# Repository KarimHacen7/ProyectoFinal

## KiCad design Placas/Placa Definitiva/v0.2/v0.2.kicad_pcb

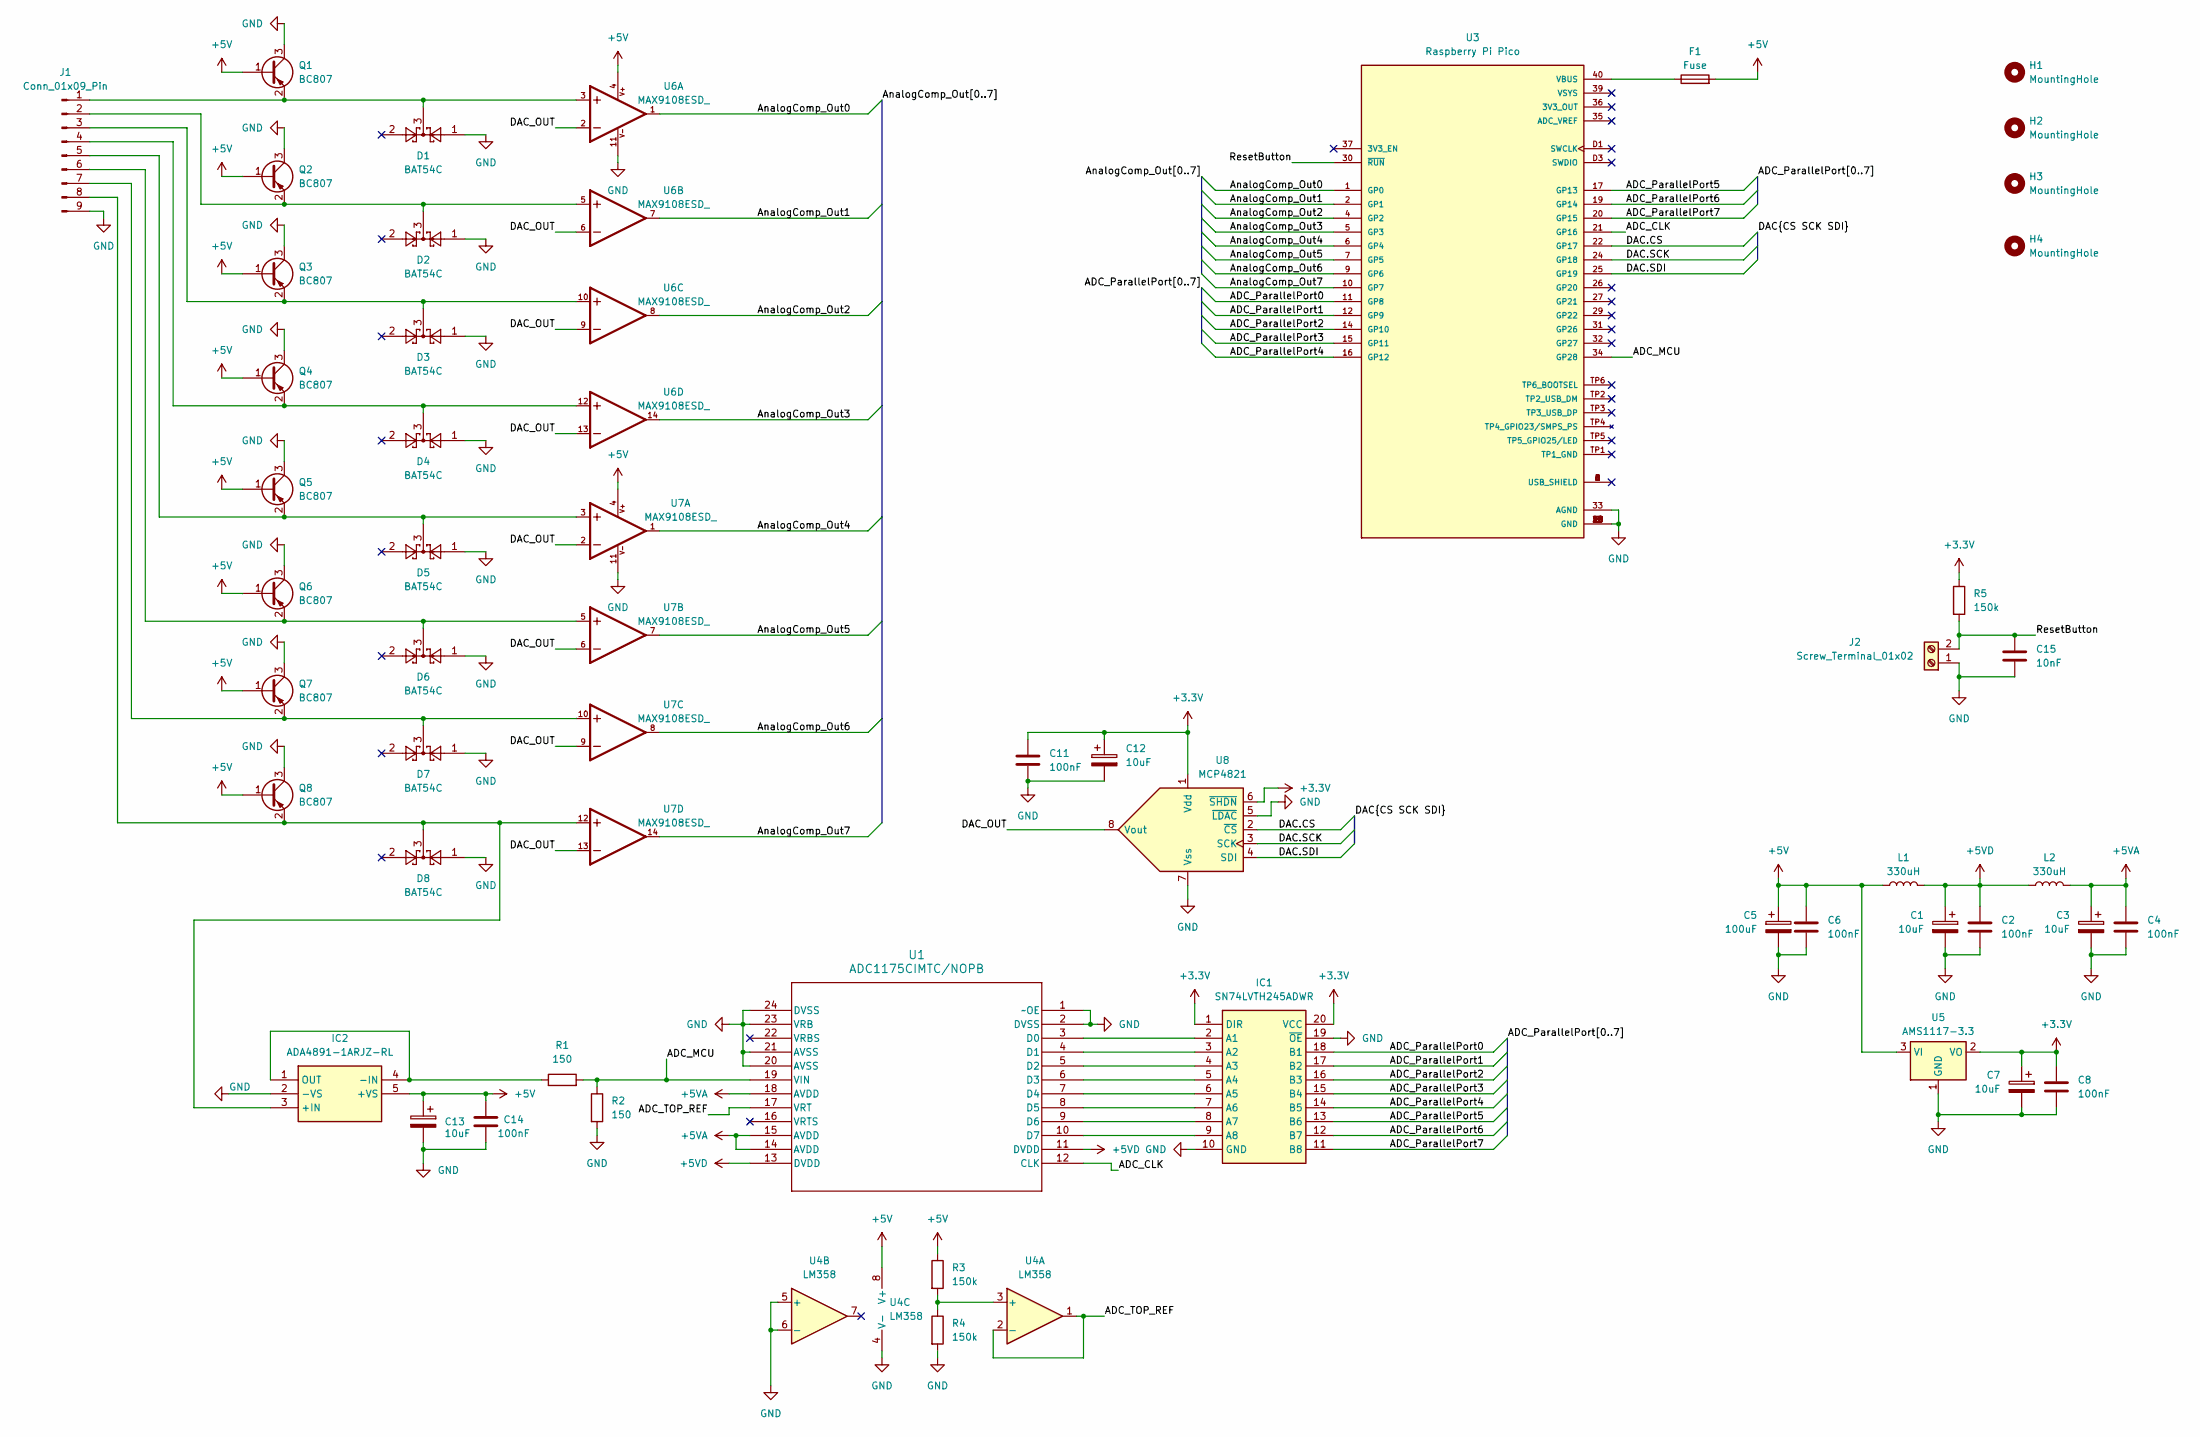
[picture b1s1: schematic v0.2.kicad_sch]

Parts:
C1, C3, C7, C12, C13: 10uF; CP_EIA-3528-15_AVX-H_Pad1.50x2.35mm_HandSolder
C2, C4, C6, C8, C11, C14: 100nF; C_0805_2012Metric_Pad1.18x1.45mm_HandSolder
C5: 100uF; CP_Elec_6.3x7.7
C15: 10nF; C_0805_2012Metric_Pad1.18x1.45mm_HandSolder
D1, D2, D3, D4, D5, D6, D7, D8: BAT54C; SOT-23
F1: Fuse; Fuse_1206_3216Metric_Pad1.42x1.75mm_HandSolder
H1, H2, H3, H4: MountingHole; MountingHole_2.5mm
IC1: SN74LVTH245ADWR; SOIC127P1030X265-20N; Mouser Part Number 595-SN74LVTH245ADWR
IC2: ADA4891-1ARJZ-RL; SOT95P280X145-5N; Mouser Part Number 584-ADA4891-1ARJZ-R
J1: Conn_01x09_Pin; PinHeader_1x09_P2.54mm_Vertical
J2: Screw_Terminal_01x02; TerminalBlock_bornier-2_P5.08mm
L1, L2: 330uH; L_Sunlord_SWRB1205S
Q1, Q2, Q3, Q4, Q5, Q6, Q7, Q8: BC807; SOT-23
R1, R2: 150; R_1206_3216Metric_Pad1.30x1.75mm_HandSolder
R3, R4, R5: 150k; R_1206_3216Metric_Pad1.30x1.75mm_HandSolder
U1: ADC1175CIMTC/NOPB; MTC24_TEX
U3: Raspberry Pi Pico; MODULE_SC0915; PARTREV 1.9
U4: LM358; SOIC-8_3.9x4.9mm_P1.27mm
U5: AMS1117-3.3; SOT-223-3_TabPin2
U6, U7: MAX9108ESD_; SOIC127P600X175-14N
U8: MCP4821; SOIC-8_3.9x4.9mm_P1.27mm

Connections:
+3.3V: C7.1, C8.1, C11.1, C12.1, IC1.1 (DIR), IC1.20 (VCC), R5.1, U5.2 (VO), U8.1 (Vdd), U8.6 (~SHDN)
+5V: C5.1, C6.1, C13.1, C14.2, F1.2, IC2.5 (+VS), L1.1, Q1.1 (B), Q2.1 (B), Q3.1 (B), Q4.1 (B), Q5.1 (B), Q6.1 (B), Q7.1 (B), Q8.1 (B), R3.1, U4.8 (V+), U5.3 (VI), U6.4, U7.4
+5VA: C3.1, C4.1, L2.2, U1.14 (AVDD), U1.15 (AVDD), U1.18 (AVDD)
+5VD: C1.1, C2.1, L1.2, L2.1, U1.11 (DVDD), U1.13 (DVDD)
/ADC_CLK: U1.12 (CLK), U3.21 (GP16)
/ADC_MCU: R1.2, R2.1, U1.19 (VIN), U3.34 (GP28)
/ADC_ParallelPort0: IC1.18 (B1), U3.11 (GP8)
/ADC_ParallelPort1: IC1.17 (B2), U3.12 (GP9)
/ADC_ParallelPort2: IC1.16 (B3), U3.14 (GP10)
/ADC_ParallelPort3: IC1.15 (B4), U3.15 (GP11)
/ADC_ParallelPort4: IC1.14 (B5), U3.16 (GP12)
/ADC_ParallelPort5: IC1.13 (B6), U3.17 (GP13)
/ADC_ParallelPort6: IC1.12 (B7), U3.19 (GP14)
/ADC_ParallelPort7: IC1.11 (B8), U3.20 (GP15)
/ADC_TOP_REF: U1.17 (VRT), U4.1, U4.2 (-)
/AnalogComp_Out0: U3.1 (GP0), U6.1
/AnalogComp_Out1: U3.2 (GP1), U6.7
/AnalogComp_Out2: U3.4 (GP2), U6.8
/AnalogComp_Out3: U3.5 (GP3), U6.14
/AnalogComp_Out4: U3.6 (GP4), U7.1
/AnalogComp_Out5: U3.7 (GP5), U7.7
/AnalogComp_Out6: U3.9 (GP6), U7.8
/AnalogComp_Out7: U3.10 (GP7), U7.14
/DAC.CS: U3.22 (GP17), U8.2 (~CS)
/DAC.SCK: U3.24 (GP18), U8.3 (SCK)
/DAC.SDI: U3.25 (GP19), U8.4 (SDI)
/DAC_OUT: U6.2, U6.6, U6.9, U6.13, U7.2, U7.6, U7.9, U7.13, U8.8 (Vout)
/ResetButton: C15.1, J2.2, R5.2, U3.30 (~RUN)
GND: C1.2, C2.2, C3.2, C4.2, C5.2, C6.2, C7.2, C8.2, C11.2, C12.2, C13.2, C14.1, C15.2, D1.1, D2.1, D3.1, D4.1, D5.1, D6.1, D7.1, D8.1, IC1.10 (GND), IC1.19 (~OE), IC2.2 (-VS), J1.9, J2.1, Q1.3 (C), Q2.3 (C), Q3.3 (C), Q4.3 (C), Q5.3 (C), Q6.3 (C), Q7.3 (C), Q8.3 (C), R2.2, R4.2, U1.1 (~OE), U1.2 (DVSS), U1.20 (AVSS), U1.21 (AVSS), U1.23 (VRB), U1.24 (DVSS), U3.3 (GND), U3.8 (GND), U3.13 (GND), U3.18 (GND), U3.23 (GND), U3.28 (GND), U3.33 (AGND), U3.38 (GND), U3.D2 (GND), U4.4 (V-), U4.5 (+), U4.6 (-), U5.1 (GND), U6.11, U7.11, U8.5 (~LDAC), U8.7 (Vss)
unnamed: IC1.2 (A1), U1.3 (D0)
unnamed: IC1.3 (A2), U1.4 (D1)
unnamed: IC1.4 (A3), U1.5 (D2)
unnamed: IC1.5 (A4), U1.6 (D3)
unnamed: IC1.6 (A5), U1.7 (D4)
unnamed: IC1.7 (A6), U1.8 (D5)
unnamed: IC1.8 (A7), U1.9 (D6)
unnamed: IC1.9 (A8), U1.10 (D7)
unnamed: D8.3, IC2.3 (+IN), J1.8, Q8.2 (E), U7.12
unnamed: IC2.1 (OUT), IC2.4 (-IN), R1.1
unnamed: D1.3, J1.1, Q1.2 (E), U6.3
unnamed: D2.3, J1.2, Q2.2 (E), U6.5
unnamed: D3.3, J1.3, Q3.2 (E), U6.10
unnamed: D4.3, J1.4, Q4.2 (E), U6.12
unnamed: D5.3, J1.5, Q5.2 (E), U7.3
unnamed: D6.3, J1.6, Q6.2 (E), U7.5
unnamed: D7.3, J1.7, Q7.2 (E), U7.10
unnamed: F1.1, U3.40 (VBUS)
unnamed: R3.2, R4.1, U4.3 (+)

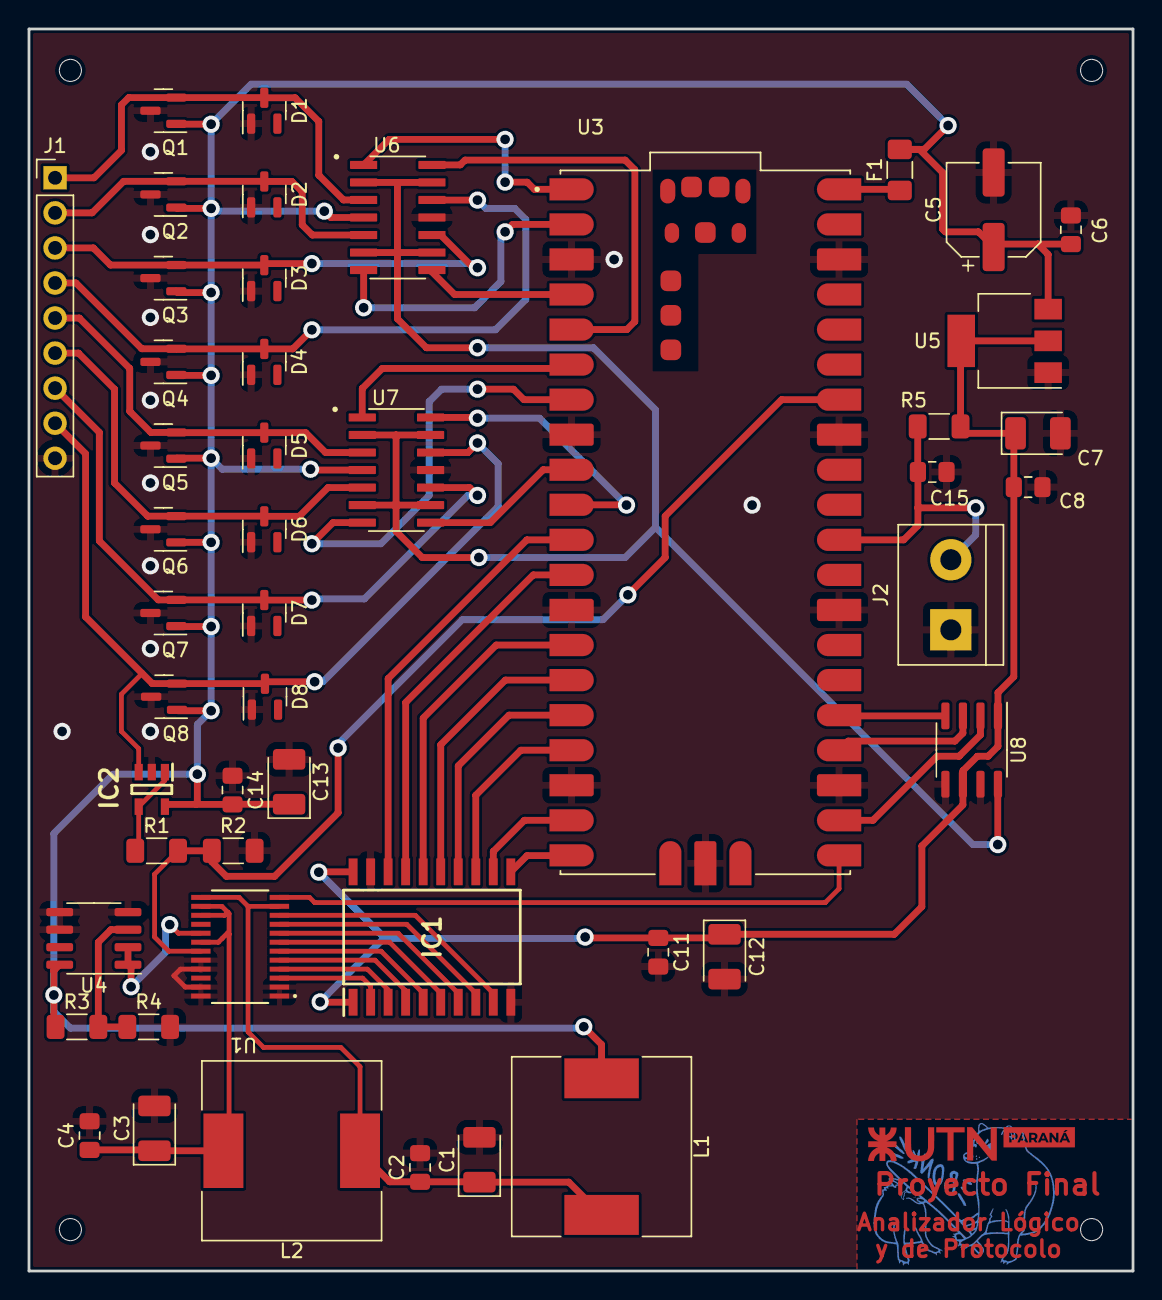
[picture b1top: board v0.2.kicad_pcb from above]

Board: 2 copper layers, 80.0 x 90.0 mm, 52 parts (0 on the bottom side), 48 nets.

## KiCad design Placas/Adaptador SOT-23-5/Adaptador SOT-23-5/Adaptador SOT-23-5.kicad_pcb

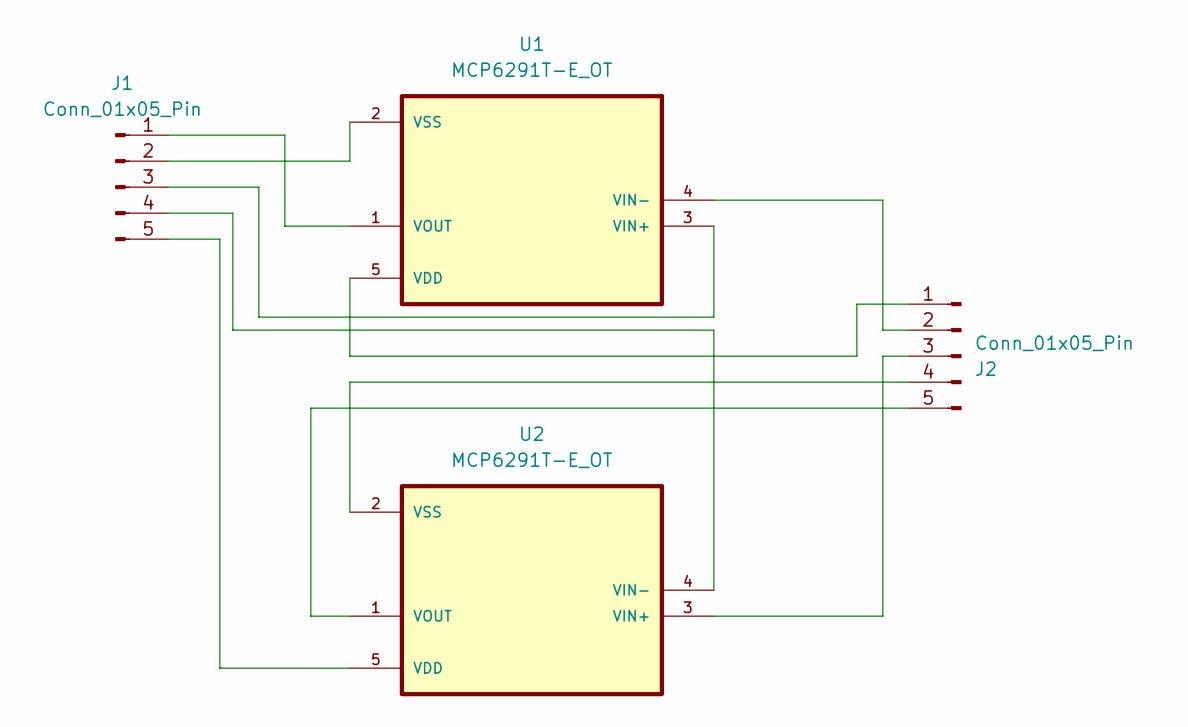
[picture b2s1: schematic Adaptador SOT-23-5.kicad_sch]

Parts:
J1, J2: Conn_01x05_Pin; PinSocket_1x05_P2.54mm_Vertical
U1, U2: MCP6291T-E_OT; SOT95P280X145-5N

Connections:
unnamed: J1.1, U1.1 (VOUT)
unnamed: J1.2, U1.2 (VSS)
unnamed: J1.3, U1.3 (VIN+)
unnamed: J1.4, U2.4 (VIN-)
unnamed: J1.5, U2.5 (VDD)
unnamed: J2.1, U1.5 (VDD)
unnamed: J2.2, U1.4 (VIN-)
unnamed: J2.3, U2.3 (VIN+)
unnamed: J2.4, U2.2 (VSS)
unnamed: J2.5, U2.1 (VOUT)

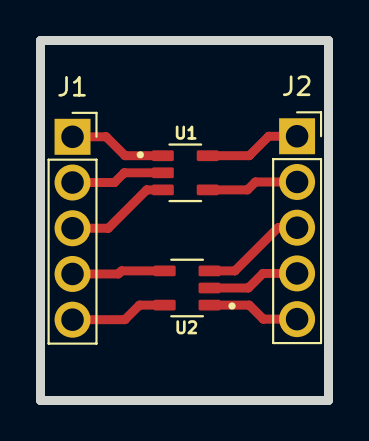
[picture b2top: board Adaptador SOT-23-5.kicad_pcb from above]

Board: 2 copper layers, 16.0 x 20.0 mm, 4 parts (0 on the bottom side), 10 nets.

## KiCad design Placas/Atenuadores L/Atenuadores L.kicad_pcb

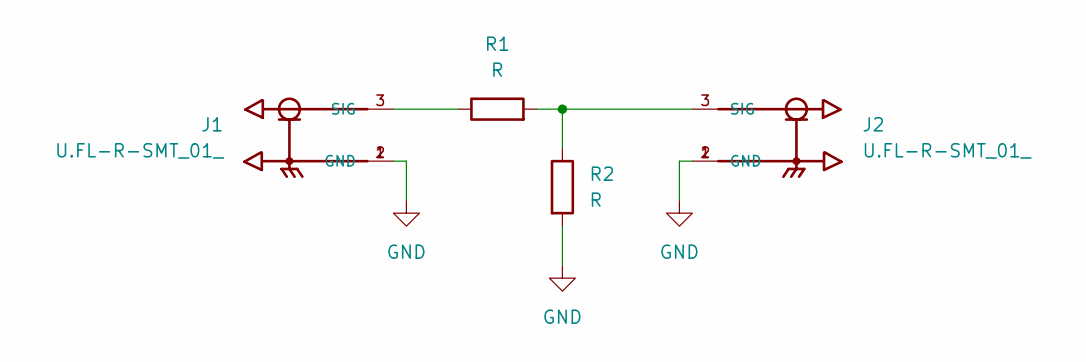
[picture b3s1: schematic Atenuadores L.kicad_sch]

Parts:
J1, J2: U.FL-R-SMT_01_; HRS_U.FL-R-SMT_01_
R1, R2: R; R_Axial_DIN0614_L14.3mm_D5.7mm_P15.24mm_Horizontal

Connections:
GND: J1.1 (GND), J1.2 (GND), J2.1 (GND), J2.2 (GND), R2.2
unnamed: J1.3 (SIG), R1.1
unnamed: J2.3 (SIG), R1.2, R2.1

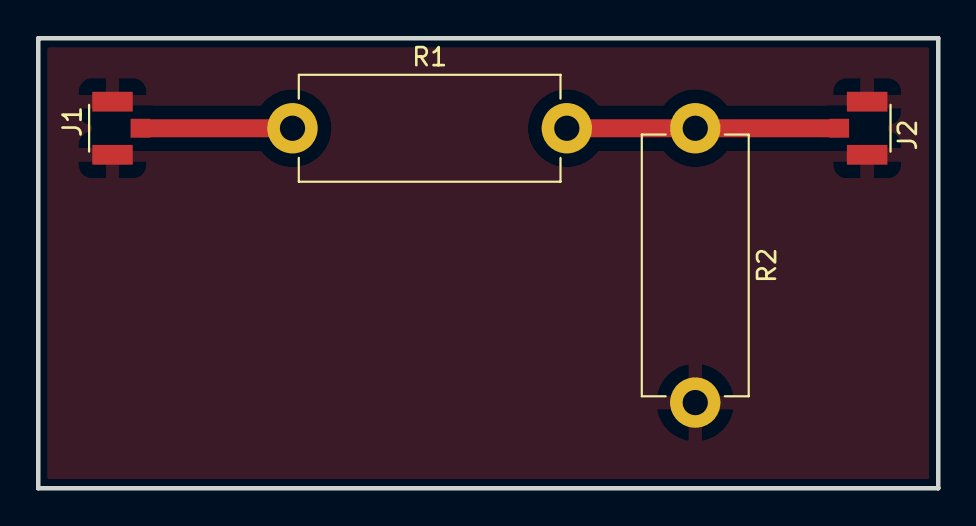
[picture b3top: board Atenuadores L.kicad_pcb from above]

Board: 2 copper layers, 50.0 x 25.0 mm, 4 parts (0 on the bottom side), 3 nets.

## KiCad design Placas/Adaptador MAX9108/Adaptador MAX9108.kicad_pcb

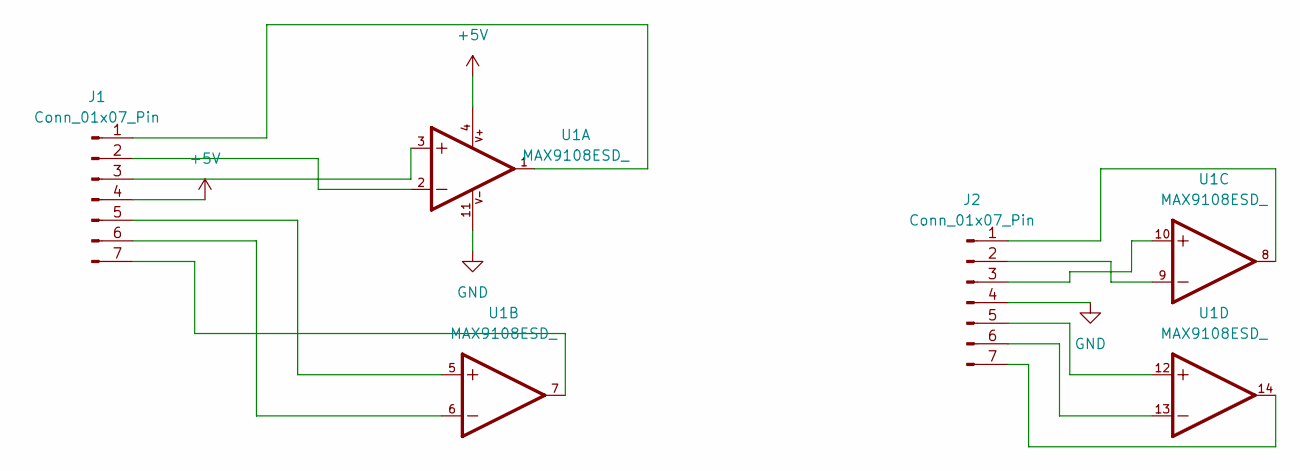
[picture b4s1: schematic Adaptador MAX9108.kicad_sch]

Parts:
J1, J2: Conn_01x07_Pin; PinHeader_1x07_P2.54mm_Vertical
U1: MAX9108ESD_; SOIC127P600X175-14N

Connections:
+5V: J1.4, U1.4
GND: J2.4, U1.11
unnamed: J1.1, U1.1
unnamed: J1.2, U1.2
unnamed: J1.3, U1.3
unnamed: J1.5, U1.5
unnamed: J1.6, U1.6
unnamed: J1.7, U1.7
unnamed: J2.1, U1.8
unnamed: J2.2, U1.9
unnamed: J2.3, U1.10
unnamed: J2.5, U1.12
unnamed: J2.6, U1.13
unnamed: J2.7, U1.14

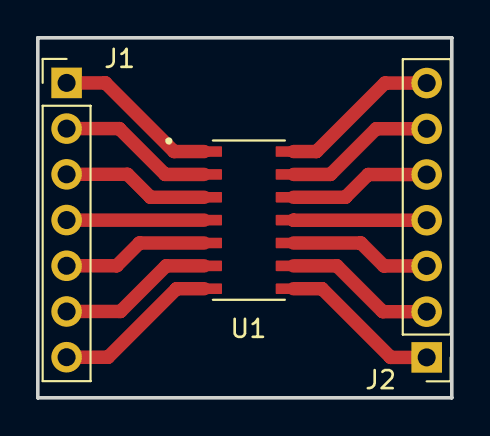
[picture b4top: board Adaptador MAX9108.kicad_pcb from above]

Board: 2 copper layers, 23.0 x 20.0 mm, 3 parts (0 on the bottom side), 14 nets.

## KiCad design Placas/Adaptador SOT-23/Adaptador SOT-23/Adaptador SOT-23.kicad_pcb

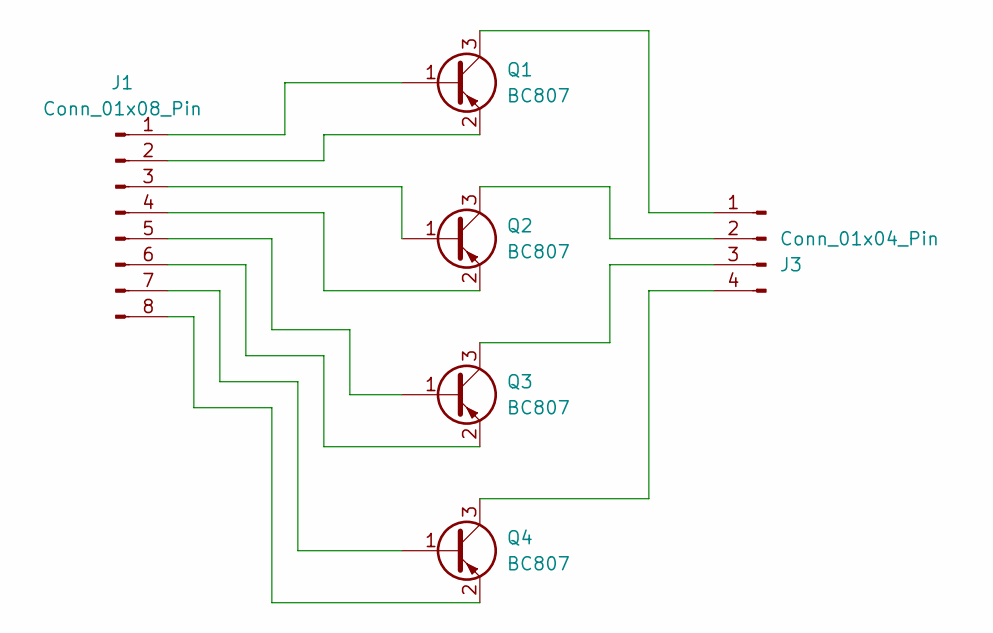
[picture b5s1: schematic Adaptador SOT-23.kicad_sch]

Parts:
J1: Conn_01x08_Pin; PinHeader_1x08_P2.54mm_Vertical
J3: Conn_01x04_Pin; PinHeader_1x04_P2.54mm_Vertical
Q1, Q2, Q3, Q4: BC807; SOT-23

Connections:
unnamed: J1.1, Q1.1 (B)
unnamed: J1.2, Q1.2 (E)
unnamed: J1.3, Q2.1 (B)
unnamed: J1.4, Q2.2 (E)
unnamed: J1.5, Q3.1 (B)
unnamed: J1.6, Q3.2 (E)
unnamed: J1.7, Q4.1 (B)
unnamed: J1.8, Q4.2 (E)
unnamed: J3.1, Q1.3 (C)
unnamed: J3.2, Q2.3 (C)
unnamed: J3.3, Q3.3 (C)
unnamed: J3.4, Q4.3 (C)

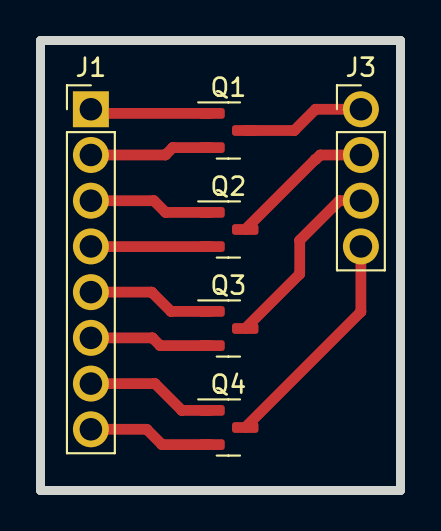
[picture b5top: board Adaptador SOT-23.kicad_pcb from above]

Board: 2 copper layers, 20.0 x 25.0 mm, 6 parts (0 on the bottom side), 12 nets.

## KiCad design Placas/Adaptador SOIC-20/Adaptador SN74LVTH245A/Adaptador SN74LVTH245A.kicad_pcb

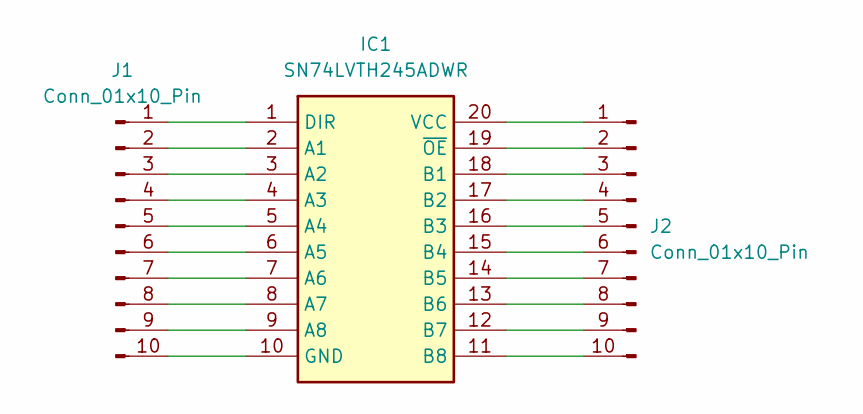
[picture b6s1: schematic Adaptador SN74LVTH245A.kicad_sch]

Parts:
IC1: SN74LVTH245ADWR; SOIC127P1030X265-20N; Mouser Part Number 595-SN74LVTH245ADWR
J1, J2: Conn_01x10_Pin; PinHeader_1x10_P2.54mm_Vertical

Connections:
unnamed: IC1.2 (A1), J1.2
unnamed: IC1.3 (A2), J1.3
unnamed: IC1.4 (A3), J1.4
unnamed: IC1.5 (A4), J1.5
unnamed: IC1.6 (A5), J1.6
unnamed: IC1.7 (A6), J1.7
unnamed: IC1.8 (A7), J1.8
unnamed: IC1.9 (A8), J1.9
unnamed: IC1.18 (B1), J2.3
unnamed: IC1.17 (B2), J2.4
unnamed: IC1.16 (B3), J2.5
unnamed: IC1.15 (B4), J2.6
unnamed: IC1.14 (B5), J2.7
unnamed: IC1.13 (B6), J2.8
unnamed: IC1.12 (B7), J2.9
unnamed: IC1.11 (B8), J2.10
unnamed: IC1.1 (DIR), J1.1
unnamed: IC1.10 (GND), J1.10
unnamed: IC1.20 (VCC), J2.1
unnamed: IC1.19 (~OE), J2.2

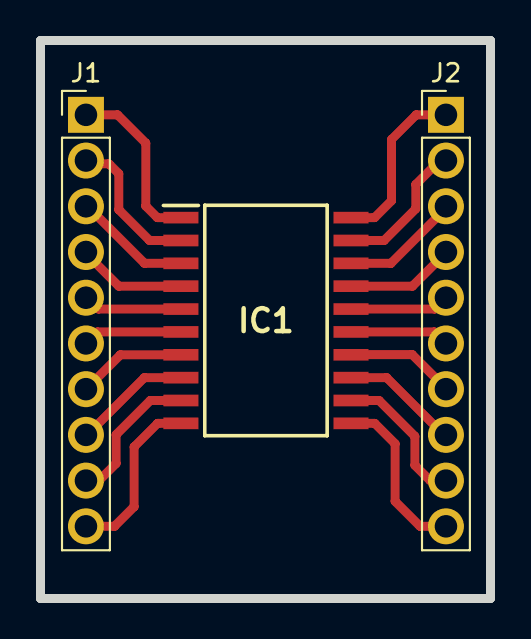
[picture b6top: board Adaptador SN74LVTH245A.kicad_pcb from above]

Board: 2 copper layers, 25.0 x 31.0 mm, 3 parts (0 on the bottom side), 20 nets.

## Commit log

2023-08-04 tratando de cargar algo
2024-03-20 Primera carga del repo de firmware
2024-03-22 ANDANDO LA WEA
2024-04-03 skere
2024-04-11 que aburrido poner mensajes
2024-04-15 carteles de estado estan buggy
2024-04-17 QTHREAD SUPPORT ADDED
2024-04-18 Added qthread support in commms
2024-04-30 Channel Plotting somewhat functional
2024-05-09 added buggy time axis
2024-05-14 Added support for zoom and scroll
2024-05-14 Upgraded cursor behavior
2024-05-15 Upgraded cursors and efficiency, bugfixing
2024-05-16 Decent perfomance upgrades
2024-05-17 Bugfixing, clarity and performance
2024-05-17 Bugfixing and proper axis drawing
2024-05-21 Cursor blitting and optimization, unfinished edge search
2024-05-21 Somewhat fixed event locator, reorganized GUI
2024-05-23 its late and i dont recall
2024-05-24 Aesthetic upgrades and DARK mode
2024-05-24 Analog mode support and upgraded event search, bugfixing
2024-05-27 bugfixing
2024-05-30 bugfix, some analyzer functionality and GUI basics
2024-06-05 Added binary decode and uart decode
2024-06-07 Added support for SPI decoding
2024-06-14 Some protocol decoding support
2024-06-19 UI updates and protocol analysis debug
2024-06-24 More protocol decoding and bugfixing
2024-07-05 I think this is ready
2024-07-31 Final commit before presentation, hopefully
2024-08-27 added report
